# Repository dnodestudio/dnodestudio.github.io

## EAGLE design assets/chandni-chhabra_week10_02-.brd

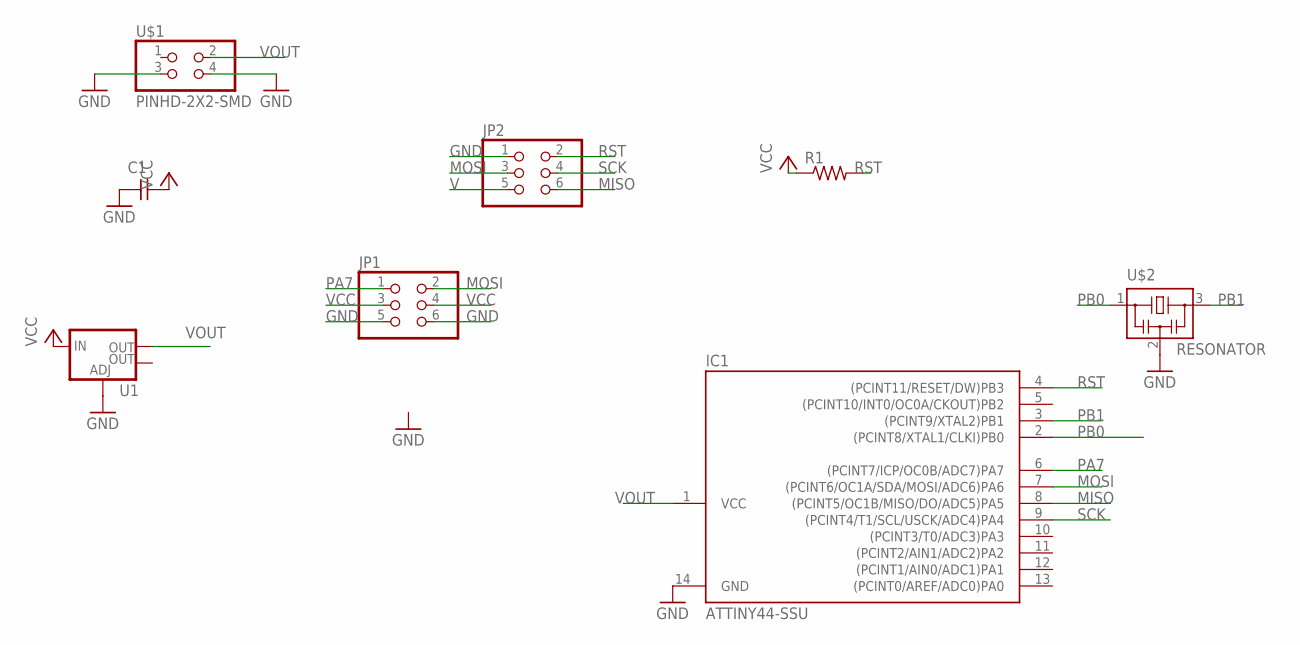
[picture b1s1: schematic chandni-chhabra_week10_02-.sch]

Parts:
C1: CAP-UNPOLARIZEDFAB; C1206FAB
IC1: ATTINY44-SSU; SOIC14
JP1, JP2: PINHD-2X3-SMD; 2X03SMD
R1: RES-US1206FAB; R1206FAB
U1: V_REG_LM1117SOT223; SOT223
U$1: PINHD-2X2-SMD; 2X02SMD
U$2: RESONATOR; EFOBM

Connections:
GND: C1.1, IC1.14 (GND), JP1.5, JP1.6, JP2.1, U1.1 (ADJ), U$1.3, U$1.4, U$2.2
MISO: IC1.8 ((PCINT5/OC1B/MISO/DO/ADC5)PA5), JP2.6
MOSI: IC1.7 ((PCINT6/OC1A/SDA/MOSI/ADC6)PA6), JP1.2, JP2.3
PA7: IC1.6 ((PCINT7/ICP/OC0B/ADC7)PA7), JP1.1
PB0: IC1.2 ((PCINT8/XTAL1/CLKI)PB0), U$2.1
PB1: IC1.3 ((PCINT9/XTAL2)PB1), U$2.3
RST: IC1.4 ((PCINT11/RESET/DW)PB3), JP2.2, R1.2
SCK: IC1.9 ((PCINT4/T1/SCL/USCK/ADC4)PA4), JP2.4
V: JP2.5
VCC: C1.2, JP1.3, JP1.4, R1.1, U1.3 (IN)
VOUT: IC1.1 (VCC), U1.2 (OUT), U$1.2

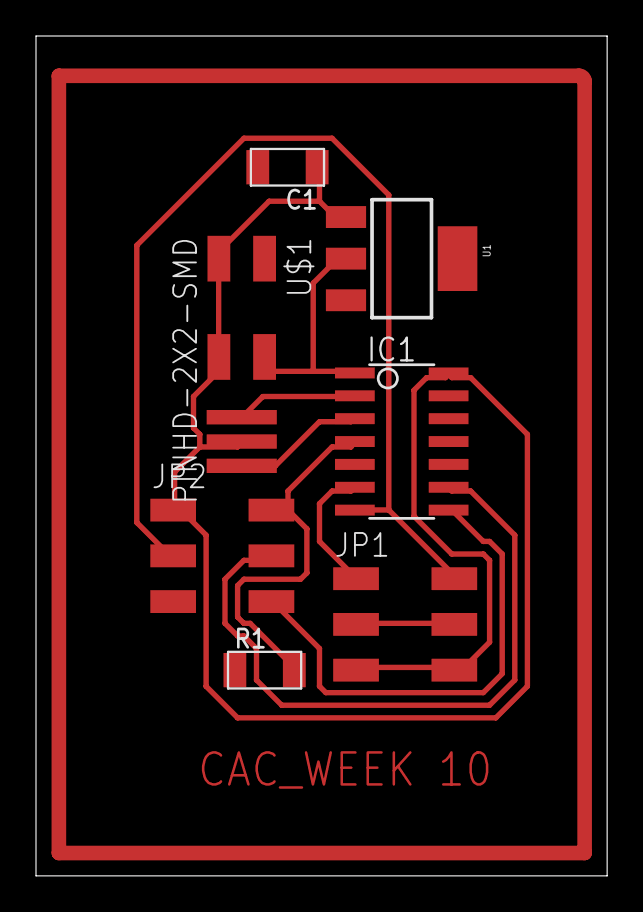
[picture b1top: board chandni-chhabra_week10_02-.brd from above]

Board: 2 copper layers, 31.7 x 46.7 mm, 8 parts (0 on the bottom side), 10 nets.

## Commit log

2018-03-09 Create cname
2018-03-09 Rename cname to CNAME
2018-06-13 CHandni Port
2018-06-14 Muse testing
2018-06-14 Test done
